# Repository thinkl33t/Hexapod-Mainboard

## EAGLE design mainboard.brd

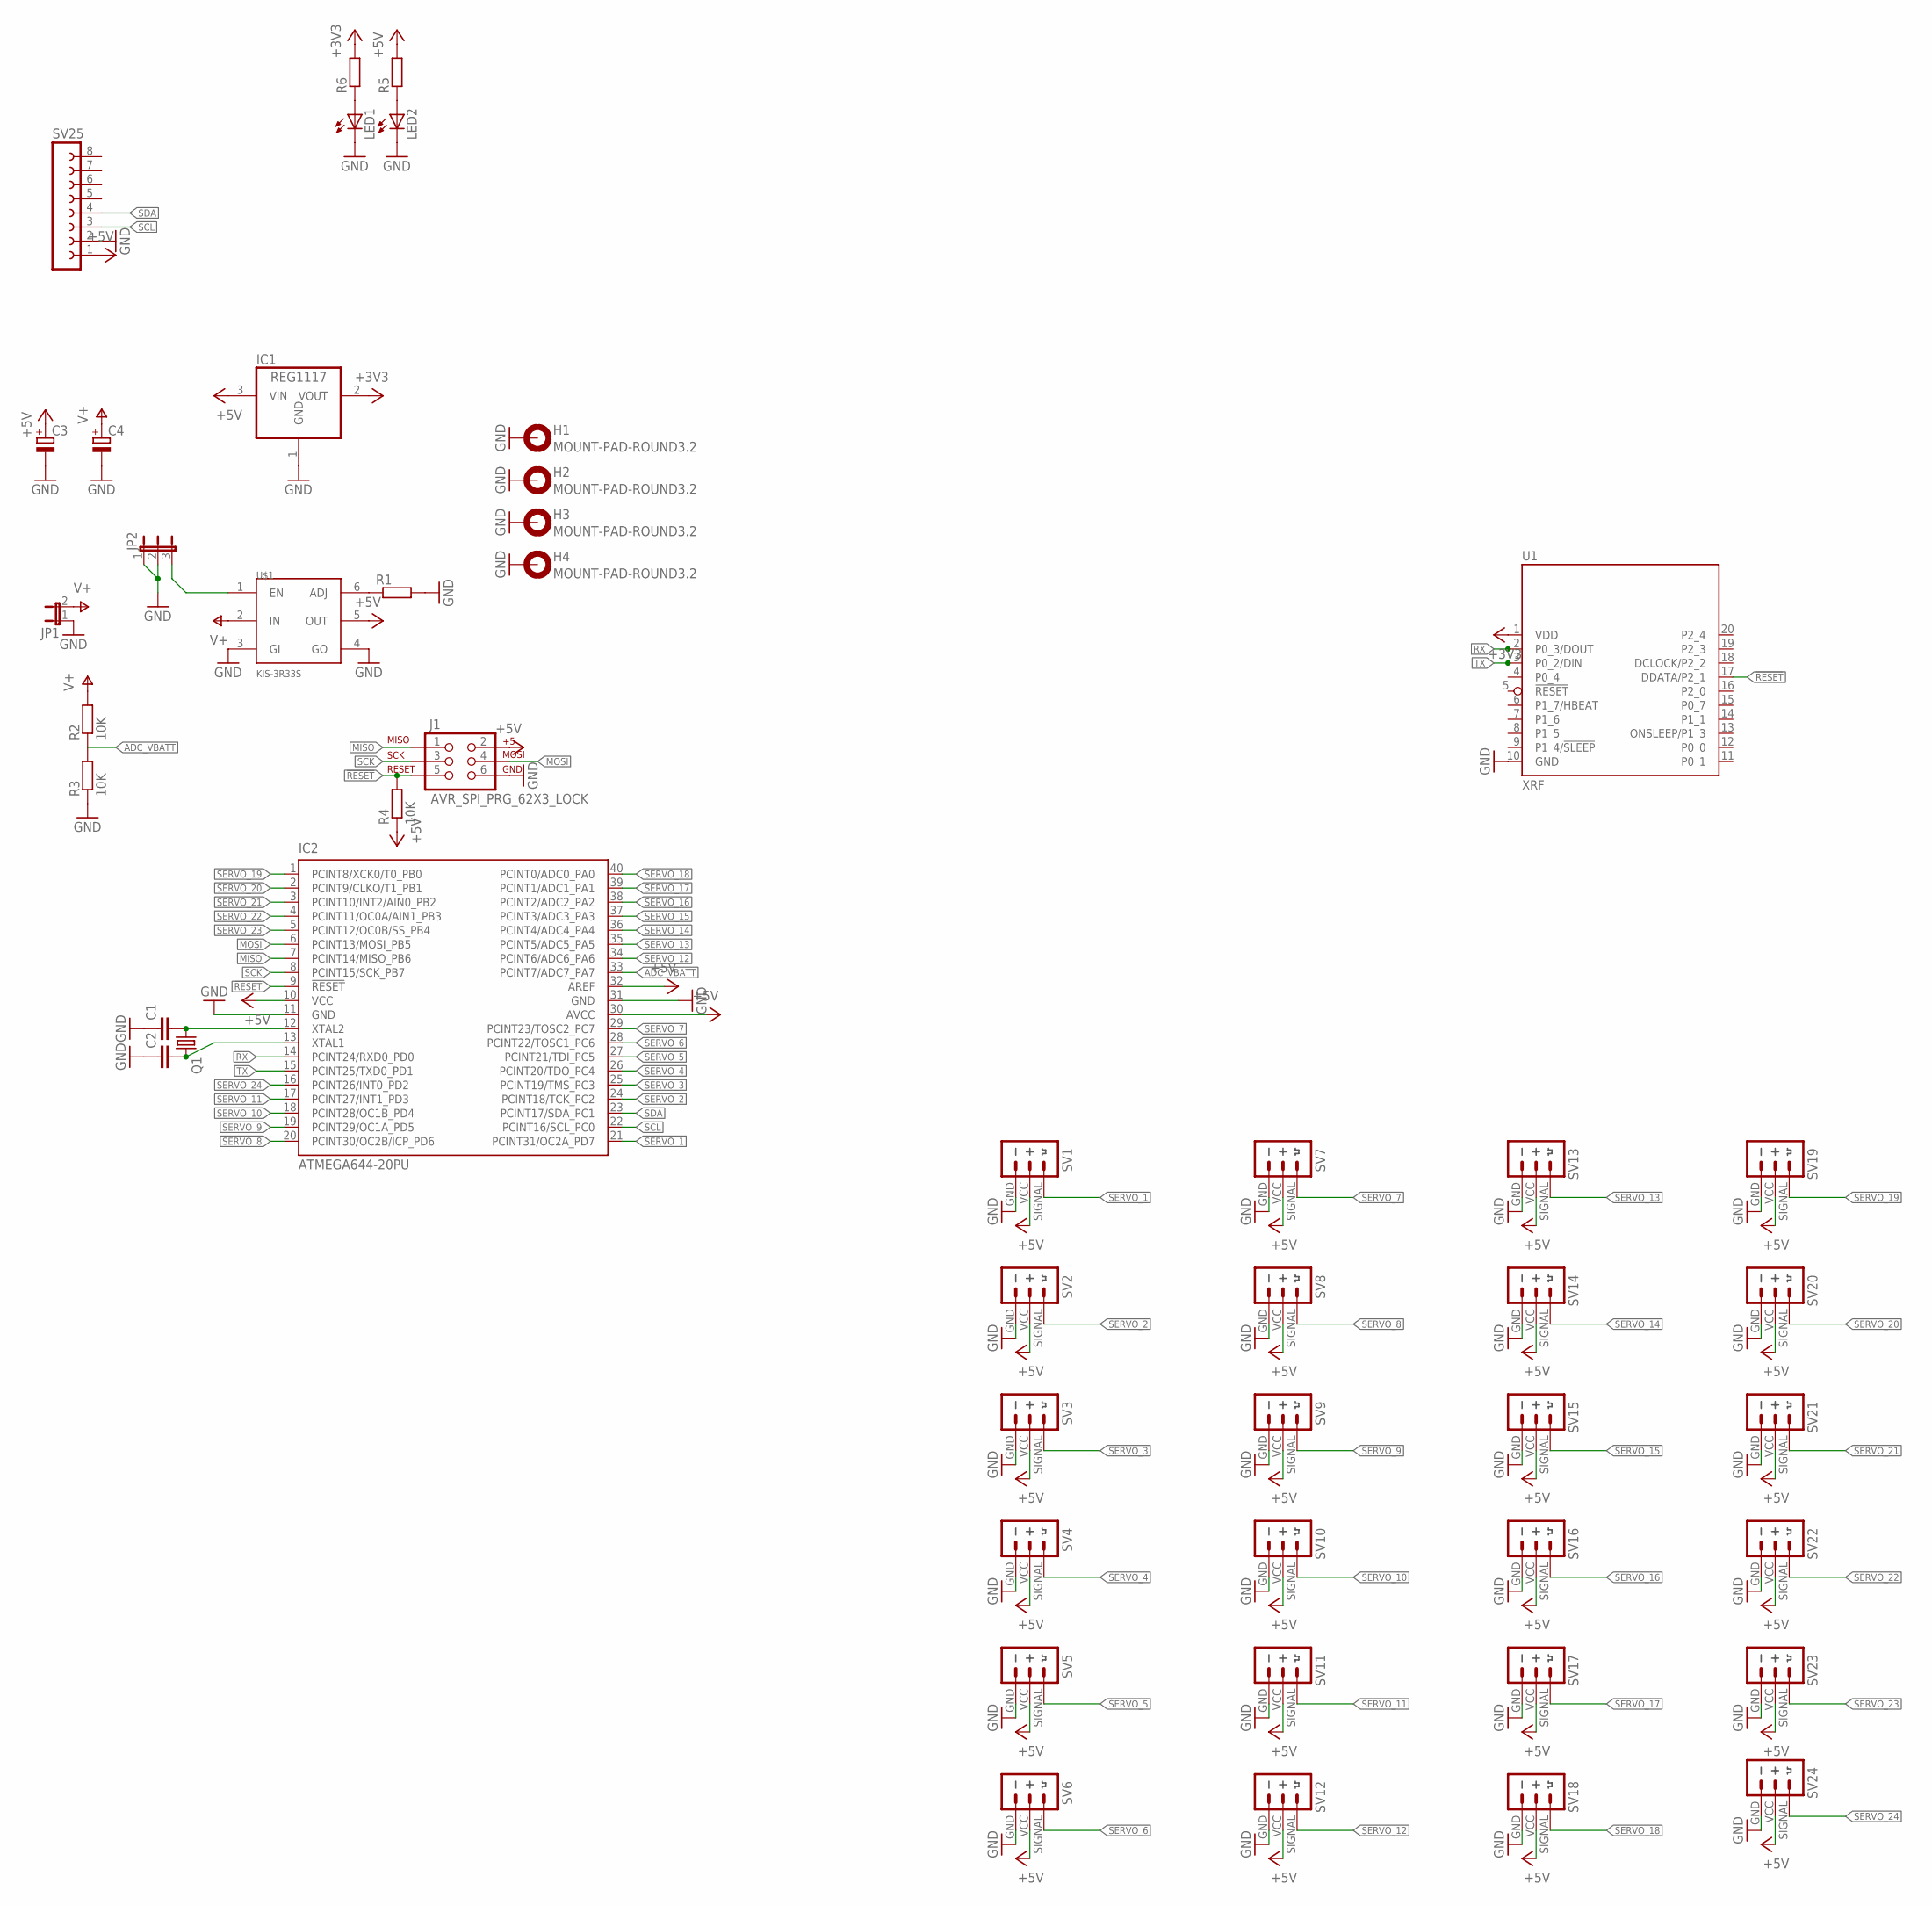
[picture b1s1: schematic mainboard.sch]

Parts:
C1, C2: C-EU025-025X050; C025-025X050
C3, C4: CPOL-EUE2.5-7; E2,5-7
H1, H2, H3, H4: MOUNT-PAD-ROUND3.2; 3,2-PAD
IC1: REG1117; SOT223
IC2: ATMEGA644-20PU; DIL40
J1: AVR_SPI_PRG_62X3_LOCK; 2X3_LOCK
JP1: JP1E; JP1
JP2: JP2E; JP2
LED1, LED2: LED5MM
Q1: CRYSTALHC49U-V; HC49U-V
R1: R-EU_0207/10; 0207/10
R2, R3: 10K; 0204/5
R4: 10K; 0204V
R5, R6: R-EU_0204/2V; 0204V
SV1, SV2, SV3, SV4, SV5, SV6, SV7, SV8, SV9, SV10, SV11, SV12, SV13, SV14, SV15, SV16, SV17, SV18, SV19, SV20, SV21, SV22, SV23, SV24: SERVO
SV25: FE08-1; FE08
U1: XRF
U$1: KIS-3R33S

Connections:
!RESET: IC2.9 (!RESET), J1.5, R4.2, U1.17 (DDATA/P2_1)
+3V3: IC1.2 (VOUT), R6.2, U1.1 (VDD)
+5V: C3.+, IC1.3 (VIN), IC2.10 (VCC), IC2.30 (AVCC), IC2.32 (AREF), J1.2, R4.1, R5.2, SV1.VCC, SV2.VCC, SV3.VCC, SV4.VCC, SV5.VCC, SV6.VCC, SV7.VCC, SV8.VCC, SV9.VCC, SV10.VCC, SV11.VCC, SV12.VCC, SV13.VCC, SV14.VCC, SV15.VCC, SV16.VCC, SV17.VCC, SV18.VCC, SV19.VCC, SV20.VCC, SV21.VCC, SV22.VCC, SV23.VCC, SV24.VCC, SV25.1, U$1.5 (OUT)
ADC_VBATT: IC2.33 (PCINT7/ADC7_PA7), R2.1, R3.2
GND: C1.1, C2.1, C3.-, C4.-, H1.B3,2, H2.B3,2, H3.B3,2, H4.B3,2, IC1.1 (GND), IC2.11 (GND), IC2.31 (GND), J1.6, JP1.1, JP2.1, JP2.2, LED1.K (C), LED2.K (C), R1.2, R3.1, SV1.GND, SV2.GND, SV3.GND, SV4.GND, SV5.GND, SV6.GND, SV7.GND, SV8.GND, SV9.GND, SV10.GND, SV11.GND, SV12.GND, SV13.GND, SV14.GND, SV15.GND, SV16.GND, SV17.GND, SV18.GND, SV19.GND, SV20.GND, SV21.GND, SV22.GND, SV23.GND, SV24.GND, SV25.2, U1.10 (GND), U$1.3 (GI), U$1.4 (GO)
MISO: IC2.7 (PCINT14/MISO_PB6), J1.1
MOSI: IC2.6 (PCINT13/MOSI_PB5), J1.4
unnamed: R1.1, U$1.6 (ADJ)
unnamed: C1.2, IC2.12 (XTAL2), Q1.1
unnamed: C2.2, IC2.13 (XTAL1), Q1.2
unnamed: JP2.3, U$1.1 (EN)
unnamed: LED2.A, R5.1
unnamed: LED1.A, R6.1
RX: IC2.14 (PCINT24/RXD0_PD0), U1.2 (P0_3/DOUT)
SCK: IC2.8 (PCINT15/SCK_PB7), J1.3
SCL: IC2.22 (PCINT16/SCL_PC0), SV25.3
SDA: IC2.23 (PCINT17/SDA_PC1), SV25.4
SERVO_1: IC2.21 (PCINT31/OC2A_PD7), SV1.SIGNAL
SERVO_2: IC2.24 (PCINT18/TCK_PC2), SV2.SIGNAL
SERVO_3: IC2.25 (PCINT19/TMS_PC3), SV3.SIGNAL
SERVO_4: IC2.26 (PCINT20/TDO_PC4), SV4.SIGNAL
SERVO_5: IC2.27 (PCINT21/TDI_PC5), SV5.SIGNAL
SERVO_6: IC2.28 (PCINT22/TOSC1_PC6), SV6.SIGNAL
SERVO_7: IC2.29 (PCINT23/TOSC2_PC7), SV7.SIGNAL
SERVO_8: IC2.20 (PCINT30/OC2B/ICP_PD6), SV8.SIGNAL
SERVO_9: IC2.19 (PCINT29/OC1A_PD5), SV9.SIGNAL
SERVO_10: IC2.18 (PCINT28/OC1B_PD4), SV10.SIGNAL
SERVO_11: IC2.17 (PCINT27/INT1_PD3), SV11.SIGNAL
SERVO_12: IC2.34 (PCINT6/ADC6_PA6), SV12.SIGNAL
SERVO_13: IC2.35 (PCINT5/ADC5_PA5), SV13.SIGNAL
SERVO_14: IC2.36 (PCINT4/ADC4_PA4), SV14.SIGNAL
SERVO_15: IC2.37 (PCINT3/ADC3_PA3), SV15.SIGNAL
SERVO_16: IC2.38 (PCINT2/ADC2_PA2), SV16.SIGNAL
SERVO_17: IC2.39 (PCINT1/ADC1_PA1), SV17.SIGNAL
SERVO_18: IC2.40 (PCINT0/ADC0_PA0), SV18.SIGNAL
SERVO_19: IC2.1 (PCINT8/XCK0/T0_PB0), SV19.SIGNAL
SERVO_20: IC2.2 (PCINT9/CLKO/T1_PB1), SV20.SIGNAL
SERVO_21: IC2.3 (PCINT10/INT2/AIN0_PB2), SV21.SIGNAL
SERVO_22: IC2.4 (PCINT11/OC0A/AIN1_PB3), SV22.SIGNAL
SERVO_23: IC2.5 (PCINT12/OC0B/SS_PB4), SV23.SIGNAL
SERVO_24: IC2.16 (PCINT26/INT0_PD2), SV24.SIGNAL
TX: IC2.15 (PCINT25/TXD0_PD1), U1.3 (P0_2/DIN)
V+: C4.+, JP1.2, R2.2, U$1.2 (IN)

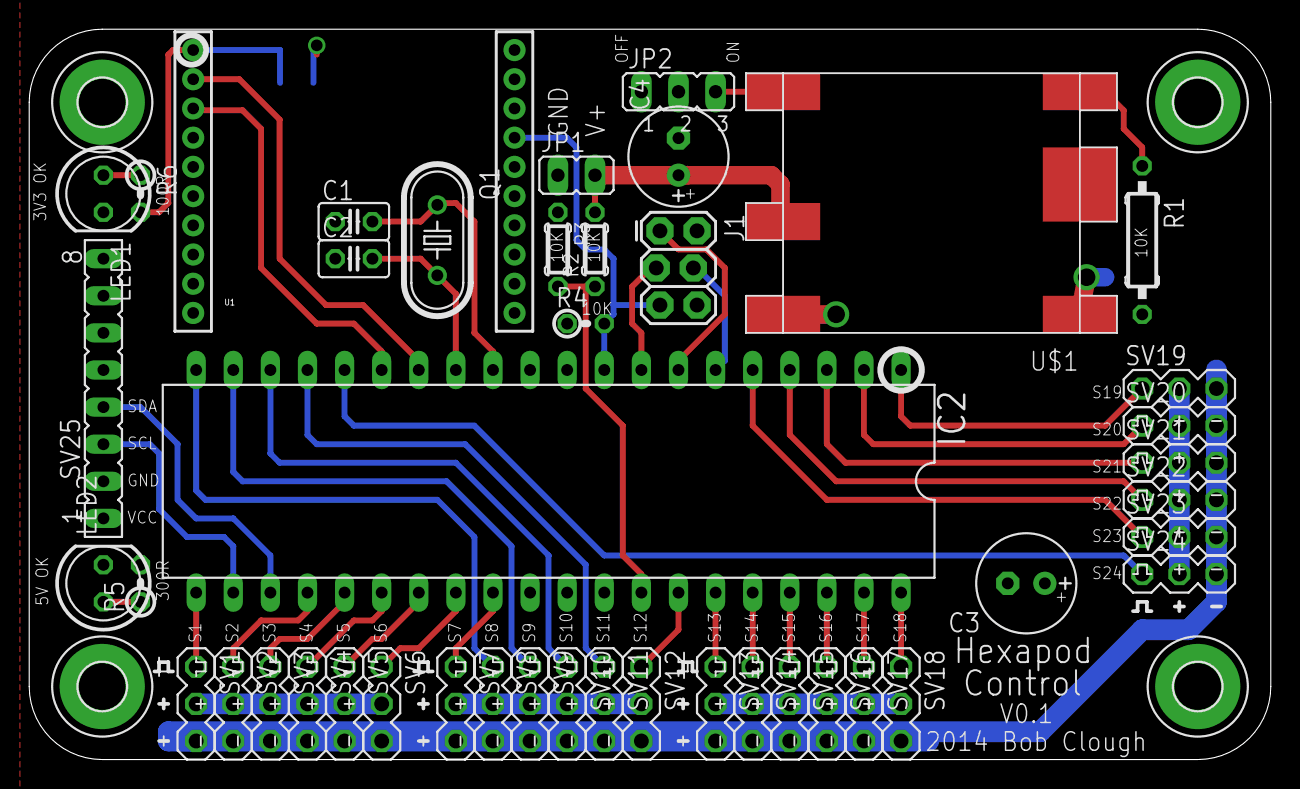
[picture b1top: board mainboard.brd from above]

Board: 2 copper layers, 85.0 x 50.0 mm, 49 parts (1 on the bottom side), 43 nets.

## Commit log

2014-07-09 V0.1
